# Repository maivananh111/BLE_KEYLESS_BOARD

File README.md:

# BLE_KEYLESS_BOARD
Keyless board esp32 for bike

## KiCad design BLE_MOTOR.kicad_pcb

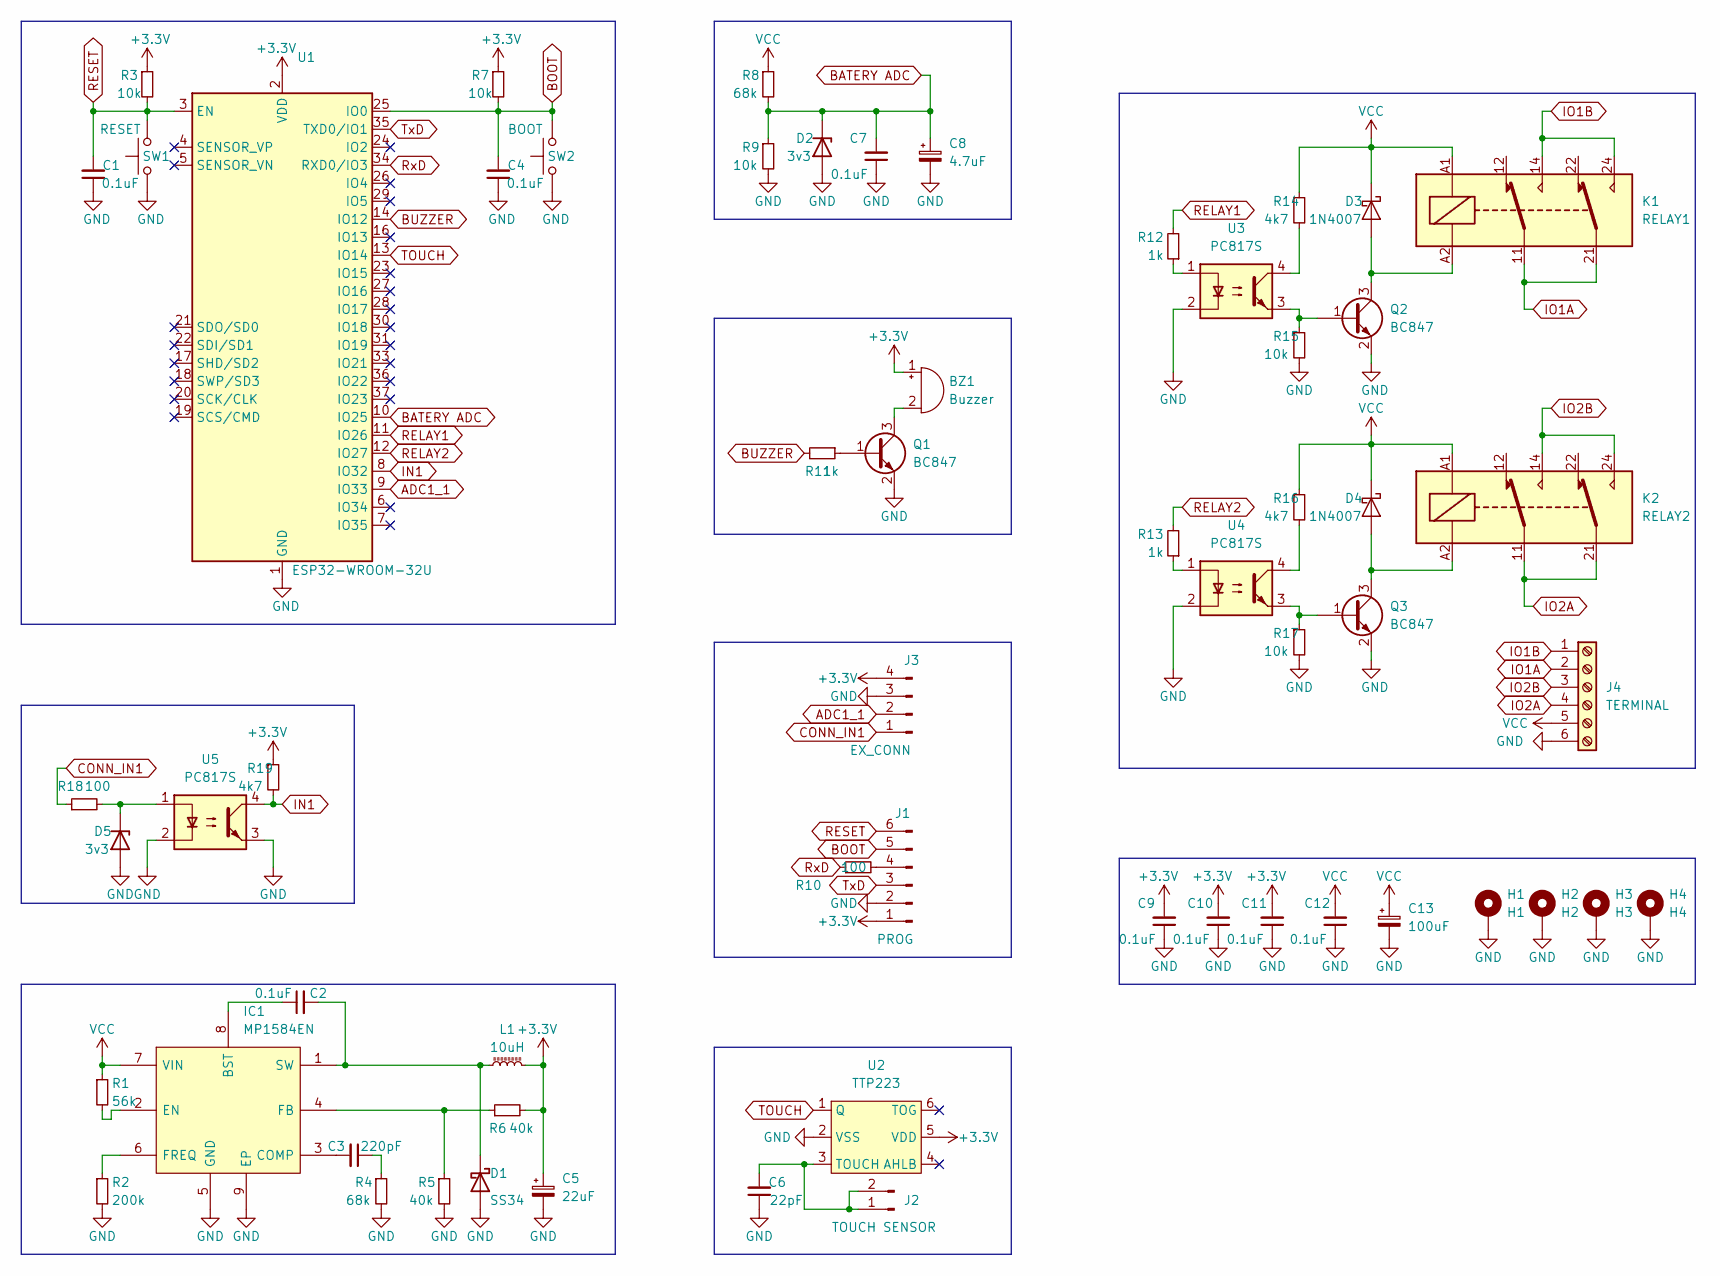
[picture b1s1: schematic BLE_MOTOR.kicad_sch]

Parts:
BZ1: Buzzer; MagneticBuzzer_PUI_AT-0927-TT-6-R
C1, C2, C4, C7, C9, C10, C11, C12: 0.1uF; C_0603_1608Metric
C3: 220pF; C_0603_1608Metric
C5: 22uF; CP_Elec_6.3x5.4
C6: 22pF; C_0603_1608Metric
C8: 4.7uF; CP_EIA-3528-12_Kemet-T
C13: 100uF; CP_Elec_6.3x5.4
D1: SS34; D_SMA
D2, D5: 3v3; D_SOD-123F
D3, D4: 1N4007; Nexperia_CFP3_SOD-123W
H1: H1; MountingHole_2.2mm_M2_Pad_Via
H2: H2; MountingHole_2.2mm_M2_Pad_Via
H3: H3; MountingHole_2.2mm_M2_Pad_Via
H4: H4; MountingHole_2.2mm_M2_Pad_Via
IC1: MP1584EN; SOIC127P600X170-9N
J1: PROG; XH_Header_2.54mm_01x06_Horizontal
J2: TOUCH SENSOR; PinHeader_1x02_P2.54mm_Vertical
J3: EX_CONN; XH_Header_2.54mm_01x04_Vertical
J4: TERMINAL; TerminalBlock_Phoenix_MKDS-1,5-6-5.08_1x06_P5.08mm_Horizont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
K1: RELAY1; Relay_DPDT_Finder_40.52
K2: RELAY2; Relay_DPDT_Finder_40.52
L1: 10uH; L_7.3x7.3_H3.5
Q1, Q2, Q3: BC847; SOT-23
R1: 56k; R_0603_1608Metric
R2: 200k; R_0603_1608Metric
R3, R7, R9, R15, R17: 10k; R_0603_1608Metric
R4, R8: 68k; R_0603_1608Metric
R5, R6: 40k; R_0603_1608Metric
R10, R18: 100; R_0603_1608Metric
R11, R12, R13: 1k; R_0603_1608Metric
R14, R16, R19: 4k7; R_0603_1608Metric
SW1: RESET; SW_SPST_CK_RS282G05A3
SW2: BOOT; SW_SPST_CK_RS282G05A3
U1: ESP32-WROOM-32U
U2: TTP223; TTP-223 SOT-23-6
U3, U4, U5: PC817S; SMDIP-4_W9.53mm

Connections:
+3.3V: BZ1.1 (-), C5.1, C9.2, C10.2, C11.2, J1.1, J3.4, L1.2, R3.1, R6.2, R7.1, R19.1, U1.2 (VDD), U2.5 (VDD)
ADC1_1: J3.2, U1.9 (IO33)
BATERY ADC: C7.2, C8.1, D2.1 (K), R8.2, R9.1, U1.10 (IO25)
BOOT: C4.2, J1.5, R7.2, SW2.2, U1.25 (IO0)
BUZZER: R11.2, U1.14 (IO12)
CONN_IN1: J3.1, R18.1
GND: C1.1, C4.1, C5.2, C6.1, C7.1, C8.2, C9.1, C10.1, C11.1, C12.1, C13.2, D1.2 (A), D2.2 (A), D5.2 (A), H1.1, H2.1, H3.1, H4.1, IC1.5 (GND), IC1.9 (EP), J1.2, J3.3, J4.6, Q1.2 (E), Q2.2 (E), Q3.2 (E), R2.2, R4.2, R5.2, R9.2, R15.2, R17.2, SW1.1, SW2.1, U1.1 (GND), U1.15 (GND), U1.38 (GND), U1.39 (GND), U2.2 (VSS), U3.2, U4.2, U5.2, U5.3
IN1: R19.2, U1.8 (IO32), U5.4
IO1A: J4.2, K1.11, K1.21
IO1B: J4.1, K1.14, K1.24
IO2A: J4.4, K2.11, K2.21
IO2B: J4.3, K2.14, K2.24
unnamed: BZ1.2 (+), Q1.3 (C)
unnamed: C2.1, IC1.8 (BST)
unnamed: C2.2, D1.1 (K), IC1.1 (SW), L1.1
unnamed: C3.1, R4.1
unnamed: C3.2, IC1.3 (COMP)
unnamed: C6.2, J2.1, J2.2, U2.3 (TOUCH)
unnamed: D3.2 (A), K1.A2, Q2.3 (C)
unnamed: D4.2 (A), K2.A2, Q3.3 (C)
unnamed: D5.1 (K), R18.2, U5.1
unnamed: IC1.2 (EN), R1.2
unnamed: IC1.4 (FB), R5.1, R6.1
unnamed: IC1.6 (FREQ), R2.1
unnamed: J1.4, R10.2
unnamed: Q1.1 (B), R11.1
unnamed: Q2.1 (B), R15.1, U3.3
unnamed: Q3.1 (B), R17.1, U4.3
unnamed: R12.1, U3.1
unnamed: R13.1, U4.1
unnamed: R14.2, U3.4
unnamed: R16.2, U4.4
RELAY1: R12.2, U1.11 (IO26)
RELAY2: R13.2, U1.12 (IO27)
RESET: C1.2, J1.6, R3.2, SW1.2, U1.3 (EN)
RxD: R10.1, U1.34 (RXD0/IO3)
TOUCH: U1.13 (IO14), U2.1 (Q)
TxD: J1.3, U1.35 (TXD0/IO1)
VCC: C12.2, C13.1, D3.1 (K), D4.1 (K), IC1.7 (VIN), J4.5, K1.A1, K2.A1, R1.1, R8.1, R14.1, R16.1

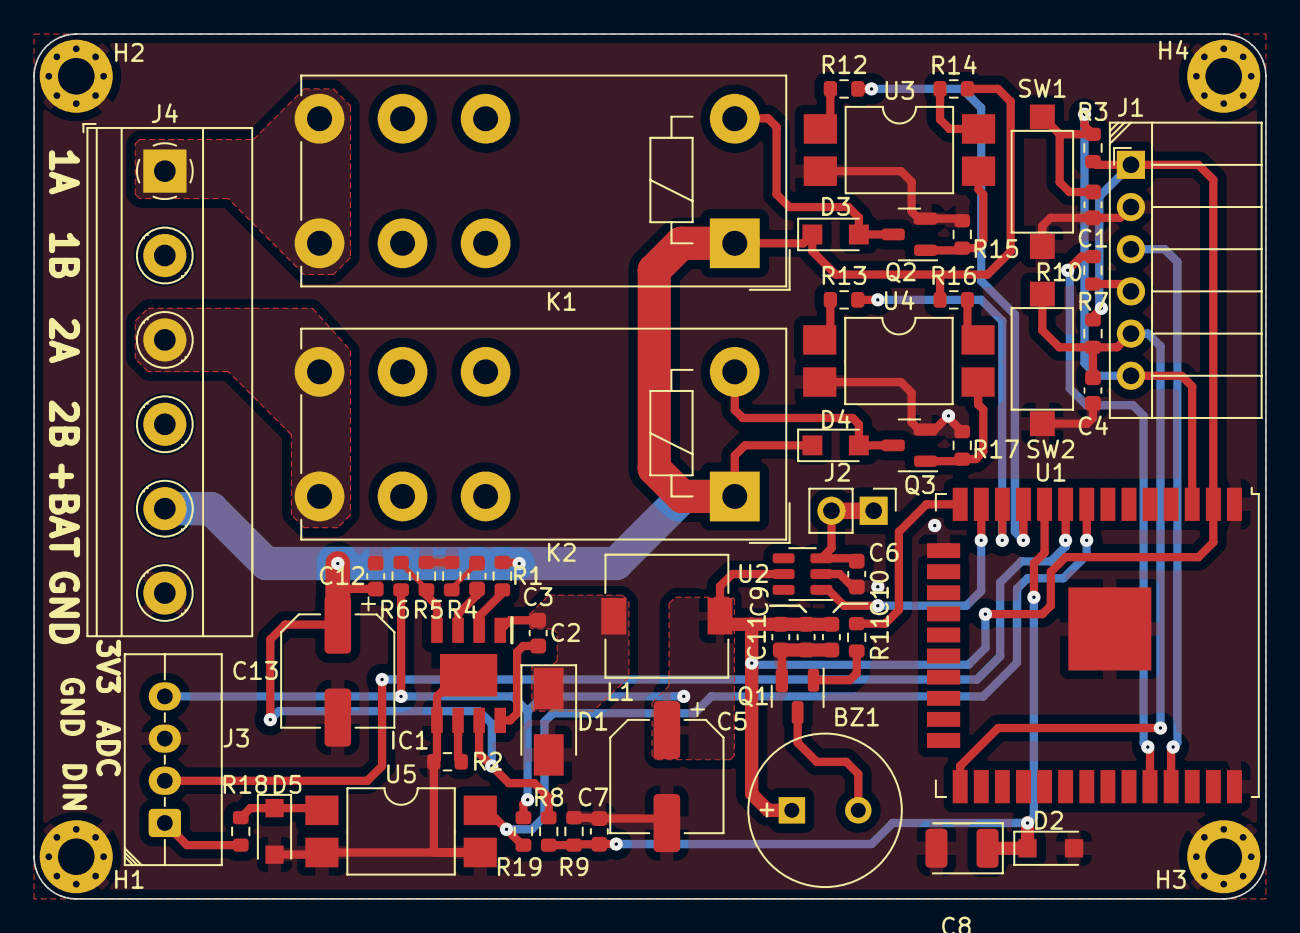
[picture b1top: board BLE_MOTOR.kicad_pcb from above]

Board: 2 copper layers, 74.2 x 52.1 mm, 60 parts (0 on the bottom side), 39 nets.
